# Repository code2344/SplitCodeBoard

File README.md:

# SplitCodeBoard

SplitCodeBoard is a split keyboard with a macropad designed for programming. I made this because I do not have any good keyboards at home, and the idea of a split keyboard appealed to me. 
SplitCodeBoard was made as part of Hack Club Stasis. "SplitCodeBoard.step" is the PCB STEP, the pcb with case is in 'SplitCodeBoard.step_STEP.zip'.
Here are some images: <br>
Macropad:<br>
<br>
Left keyboard half:<br>
<br>
Right keyboard half:<br>
<br>
Side schematic:<br>
<br>
Main and macropad schematic:<br>
<br>
PCB:<br>
<br>

## BOM
| Name | Purpose | Quantity | Total Cost (USD) | Link | Distributor |
|------|---------|----------|------------------|------|-------------|
| MCP23017-E/SO | GPIO expansion for the nRF52840 on the keyboard sides | 2 | 3.24 | [Link to listing](https://www.digikey.com/en/products/detail/microchip-technology/MCP23017-E-SO/894271) | Digikey |
| Seeed Xiao nRF52840 | Microcontrollers | 3 | 48.54 | [Link to listing](https://www.digikey.com.au/en/products/detail/seeed-technology-co-ltd/102010448/16652893?srsltid=AfmBOopCoDCC1iggG736AFU-o5CQ8K0FazSBUvREHLvtvnr260xrHbc02Ug) | Digikey |
| Kailh PG1350 Choc V1 70PCS Mechanical Keyboard Switch Kailh Low Profile Switches Chocolate Mechanical Keyboard Switch RGB SMD 5-Pin Kailh Switches | Switches for the keyboard | 1 | 49.98 | [Link to listing](https://snapklik.com/en-au/product/kailh-pg1350-choc-v1-70pcs-mechanical-keyboard-switch-kailh-low-profile-switches-chocolate-mechanical-keyboard-switch-rgb-smd-5-pin-kailh-switches-dark-blue-70pcs/0W3L4PV7UIYW5) | Snapklik |
| Kailh Choc Hotswap Sockets (Pack of 10) | Hotswap sockets for the keys | 7 | 24.5 | [Link to listing](https://keebd.com/products/kailh-choc-hotswap-sockets?variant=40393453338776&country=AU&currency=AUD) | KEEBD |
| PURFIELD 3.7V 501012 401010 401012 400909 Polymer Lithium Battery Suitable for I7 i8 i9 i10 Earphone Headset MP3 MP4 Toy GPS | Batteries for each half of the keyboard | 20 | 21.2 | [Link to listing](https://www.aliexpress.com/item/1005008747431465.html) | Aliexpress |
| 1N5819HW-7-F | Diodes for the key matrix | 70 | 17.15 | [Link to listing](https://www.digikey.com.au/en/products/detail/diodes-incorporated/1N5819HW-7-F/814970) | Digikey |

## Licensing

This repository uses split licensing by content type:

- Firmware and firmware configuration (for example, files under `zmk-config/`) are licensed under GNU Affero General Public License v3.0 only (`AGPL-3.0-only`).
- Hardware design files (for example, KiCad schematics/PCBs, footprints, and 3D mechanical files) are licensed under CERN Open Hardware Licence Version 2 - Strongly Reciprocal (`CERN-OHL-S-2.0`).

See the root `LICENSE` file for full licensing scope and notices.

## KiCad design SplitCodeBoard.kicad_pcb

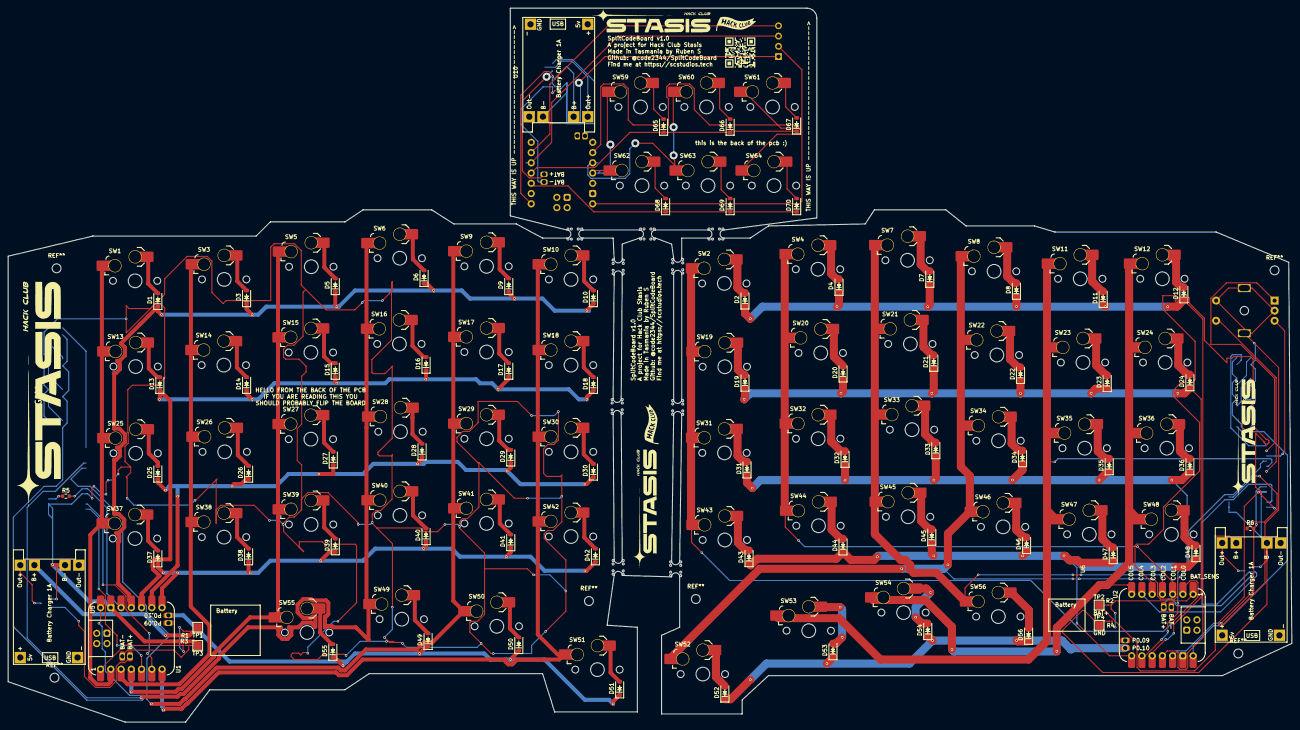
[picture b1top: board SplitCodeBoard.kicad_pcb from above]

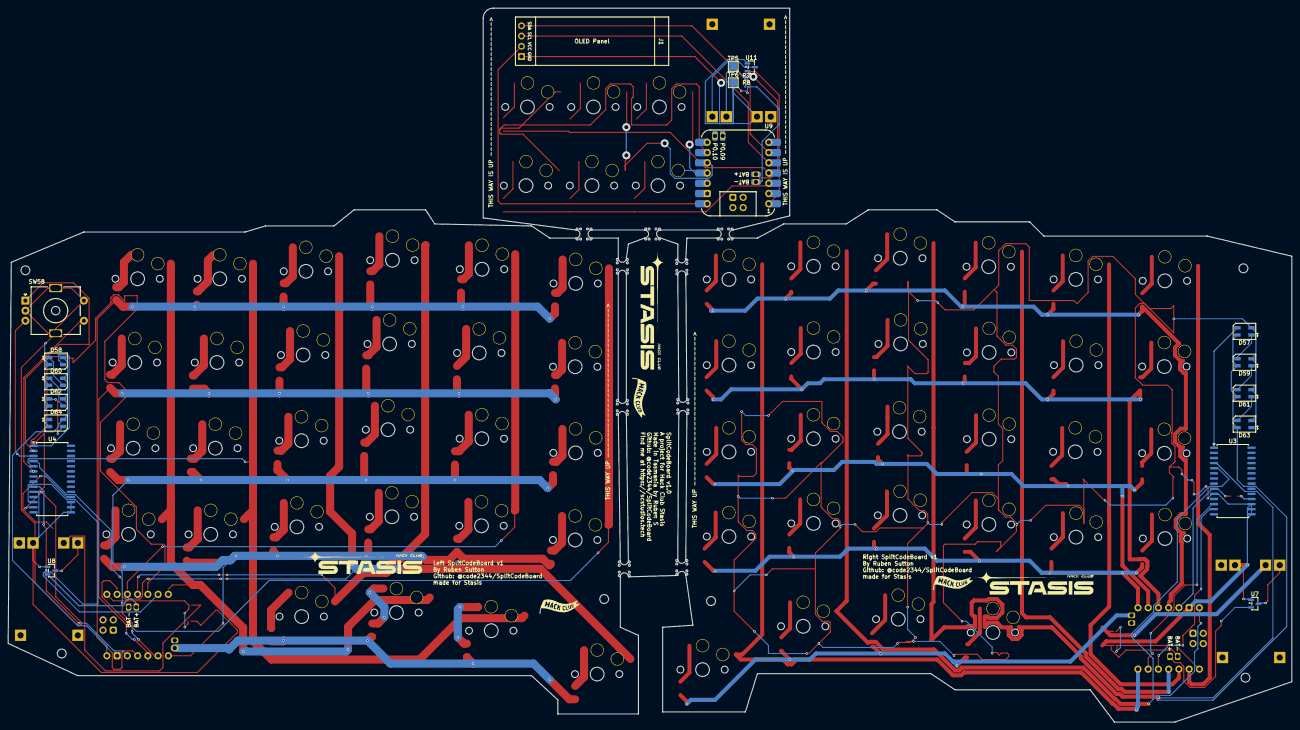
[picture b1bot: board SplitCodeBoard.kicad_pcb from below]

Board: 2 copper layers, 318.2 x 176.9 mm, 169 parts (20 on the bottom side), 124 nets.

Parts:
D1, D2, D3, D4, D5, D6, D7, D8, D9, D10, D11, D12, D13, D14, D15, D16, D17, D18, D19, D20, D21, D22, D23, D24, D25, D26, D27, D28, D29, D30, D31, D32, D33, D34, D35, D36, D37, D38, D39, D40, D41, D42, D43, D44, D45, D46, D47, D48, D49, D50, D51, D52, D53, D54, D55, D56, D65, D66, D67, D68, D69, D70: D; D_SOD-123
D57, D58, D59, D60, D61, D62, D63, D64: SK6812MINI; LED_SK6812MINI_PLCC4_3.5x3.5mm_P1.75mm
H1, H1#2, H1#3, H1#4, H1#5, H1#6, H1#7, H2, H3: MountingHole; MouseBite-Slot_2.0x2.0mm_inset_D0.5mm_P0.85mm_4h_Trace
J1: OLED; SSD1306-0.91-OLED-4pin-128x32
QR${REFERENCE}: https://scstudios.tech; httpsscstudios.tech
R1, R2, R3, R4, R7, R8: R; R_0201_0603Metric
R5, R6: 10k; R_0603_1608Metric
SW1, SW2, SW3, SW4, SW5, SW6, SW7, SW8, SW9, SW10, SW11, SW12, SW13, SW14, SW15, SW16, SW17, SW18, SW19, SW20, SW21, SW22, SW23, SW24, SW25, SW26, SW27, SW28, SW29, SW30, SW31, SW32, SW33, SW34, SW35, SW36, SW37, SW38, SW39, SW40, SW41, SW42, SW43, SW44, SW45, SW46, SW47, SW48, SW49, SW50, SW51, SW52, SW53, SW54, SW55, SW56, SW59, SW60, SW61, SW62, SW63, SW64: SW_Push; SW_choc_v1_HS_CPG135001S30_1u
SW58: RotaryEncoder_Switch_MP; RotaryEncoder_Alps_EC11E-Switch_Vertical_H20mm_MountingHoles
TP1, TP2, TP5: BAT; TestPoint_Pad_2.0x2.0mm
TP3, TP4, TP6: GND; TestPoint_Pad_2.0x2.0mm
U1, U2, U9: Seeeduino Xiao nRF52840; Xiao_nRF52840_ACH
U3, U4: MCP23017_SO; SOIC-28W_7.5x17.9mm_P1.27mm
U5, U6, U10: TP4056-18650
U7, U8, U11: MCP1700x-330xxTT; SOT-23

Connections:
+5V: D57.4 (VDD), D58.4 (VDD), D59.4 (VDD), D60.4 (VDD), D61.4 (VDD), D62.4 (VDD), D63.4 (VDD), D64.4 (VDD), J1.2, U1.8 (5V), U2.8 (5V), U9.8 (5V)
/3.3: U9.16 (BAT+), U11.2 (VO)
/BT_PIN: R7.2, R8.1, U9.1 (P0.02)
/COL1: SW59.1, SW62.1, U9.11 (P1.15)
/COL2: SW60.1, SW63.1, U9.12 (P1.14)
/COL3: SW61.1, SW64.1, U9.13 (P1.13)
/ROW1: D65.1 (K), D66.1 (K), D67.1 (K), U9.4 (P0.29)
/ROW2: D68.1 (K), D69.1 (K), D70.1 (K), U9.3 (P0.28)
/VBAT: R7.1, TP5.1, U10.5 (B+)
/left/3.3: U1.16 (BAT+), U7.2 (VO)
/left/BT_PIN: R1.2, R3.1, U1.1 (P0.02)
/left/COL0: SW1.1, SW13.1, SW25.1, SW37.1, U1.2 (P0.03)
/left/COL1: SW3.1, SW14.1, SW26.1, SW38.1, U1.3 (P0.28)
/left/COL2: SW5.1, SW15.1, SW27.1, SW39.1, SW55.1, U1.4 (P0.29)
/left/COL3: SW6.1, SW16.1, SW28.1, SW40.1, SW49.1, U3.4 (GPB3)
/left/COL4: SW9.1, SW17.1, SW29.1, SW41.1, SW50.1, U3.5 (GPB4)
/left/COL5: SW10.1, SW18.1, SW30.1, SW42.1, SW51.1, U1.7 (P1.11)
/left/ROW0: D1.1 (K), D3.1 (K), D5.1 (K), D6.1 (K), D9.1 (K), D10.1 (K), U1.11 (P1.15)
/left/ROW1: D13.1 (K), D14.1 (K), D15.1 (K), D16.1 (K), D17.1 (K), D18.1 (K), U1.12 (P1.14)
/left/ROW2: D25.1 (K), D26.1 (K), D27.1 (K), D28.1 (K), D29.1 (K), D30.1 (K), U1.13 (P1.13)
/left/ROW3: D37.1 (K), D38.1 (K), D39.1 (K), D40.1 (K), D41.1 (K), D42.1 (K), U1.14 (P1.12)
/left/ROW4: D49.1 (K), D50.1 (K), D51.1 (K), D55.1 (K), U1.18 (P0.10)
/left/VBAT: R1.1, TP1.1, U5.5 (B+)
/right/1A: SW58.A, U4.2 (GPB1)
/right/1B: SW58.B, U4.3 (GPB2)
/right/3.3: U2.16 (BAT+), U8.2 (VO)
/right/BT_PIN: R2.2, R4.1, U2.1 (P0.02)
/right/COL0: SW2.1, SW19.1, SW31.1, SW43.1, U2.2 (P0.03)
/right/COL1: SW4.1, SW20.1, SW32.1, SW44.1, U2.3 (P0.28)
/right/COL2: SW7.1, SW21.1, SW33.1, SW45.1, SW56.1, U2.4 (P0.29)
/right/COL3: SW8.1, SW22.1, SW34.1, SW46.1, SW52.1, U4.4 (GPB3)
/right/COL4: SW11.1, SW23.1, SW35.1, SW47.1, SW53.1, U4.5 (GPB4)
/right/COL5: SW12.1, SW24.1, SW36.1, SW48.1, SW54.1, U2.7 (P1.11)
/right/ROW0: D2.1 (K), D4.1 (K), D7.1 (K), D8.1 (K), D11.1 (K), D12.1 (K), U2.11 (P1.15)
/right/ROW1: D19.1 (K), D20.1 (K), D21.1 (K), D22.1 (K), D23.1 (K), D24.1 (K), U2.12 (P1.14)
/right/ROW2: D31.1 (K), D32.1 (K), D33.1 (K), D34.1 (K), D35.1 (K), D36.1 (K), U2.13 (P1.13)
/right/ROW3: D43.1 (K), D44.1 (K), D45.1 (K), D46.1 (K), D47.1 (K), D48.1 (K), U2.14 (P1.12)
/right/ROW4: D52.1 (K), D53.1 (K), D54.1 (K), D56.1 (K), U2.18 (P0.10)
/right/S1: SW58.S1, U4.6 (GPB5)
/right/VBAT: R2.1, TP2.1, U6.5 (B+)
GND: D57.2 (VSS), D58.2 (VSS), D59.2 (VSS), D60.2 (VSS), D61.2 (VSS), D62.2 (VSS), D63.2 (VSS), D64.2 (VSS), J1.1, R3.2, R4.2, R8.2, SW58.C, SW58.MP, SW58.S2, TP3.1, TP4.1, TP6.1, U1.9 (GND), U1.15 (BAT-), U2.9 (GND), U2.15 (BAT-), U3.10 (VSS), U3.15 (A0), U3.16 (A1), U3.17 (A2), U4.10 (VSS), U4.15 (A0), U4.16 (A1), U4.17 (A2), U5.6 (B-), U6.6 (B-), U7.1 (GND), U8.1 (GND), U9.15 (BAT-), U10.6 (B-), U11.1 (GND)
unnamed: D1.2 (A), SW1.2
unnamed: D2.2 (A), SW2.2
unnamed: D3.2 (A), SW3.2
unnamed: D4.2 (A), SW4.2
unnamed: D5.2 (A), SW5.2
unnamed: D6.2 (A), SW6.2
unnamed: D7.2 (A), SW7.2
unnamed: D8.2 (A), SW8.2
unnamed: D9.2 (A), SW9.2
unnamed: D10.2 (A), SW10.2
unnamed: D11.2 (A), SW11.2
unnamed: D12.2 (A), SW12.2
unnamed: D13.2 (A), SW13.2
unnamed: D14.2 (A), SW14.2
unnamed: D15.2 (A), SW15.2
unnamed: D16.2 (A), SW16.2
unnamed: D17.2 (A), SW17.2
unnamed: D18.2 (A), SW18.2
unnamed: D19.2 (A), SW19.2
unnamed: D20.2 (A), SW20.2
unnamed: D21.2 (A), SW21.2
unnamed: D22.2 (A), SW22.2
unnamed: D23.2 (A), SW23.2
unnamed: D24.2 (A), SW24.2
unnamed: D25.2 (A), SW25.2
unnamed: D26.2 (A), SW26.2
unnamed: D27.2 (A), SW27.2
unnamed: D28.2 (A), SW28.2
unnamed: D29.2 (A), SW29.2
unnamed: D30.2 (A), SW30.2
unnamed: D31.2 (A), SW31.2
unnamed: D32.2 (A), SW32.2
unnamed: D33.2 (A), SW33.2
unnamed: D34.2 (A), SW34.2
unnamed: D35.2 (A), SW35.2
unnamed: D36.2 (A), SW36.2
unnamed: D37.2 (A), SW37.2
unnamed: D38.2 (A), SW38.2
unnamed: D39.2 (A), SW39.2
unnamed: D40.2 (A), SW40.2
unnamed: D41.2 (A), SW41.2
unnamed: D42.2 (A), SW42.2
unnamed: D43.2 (A), SW43.2
unnamed: D44.2 (A), SW44.2
unnamed: D45.2 (A), SW45.2
unnamed: D46.2 (A), SW46.2
unnamed: D47.2 (A), SW47.2
unnamed: D48.2 (A), SW48.2
unnamed: D49.2 (A), SW49.2
unnamed: D50.2 (A), SW50.2
unnamed: D51.2 (A), SW51.2
unnamed: D52.2 (A), SW52.2
unnamed: D53.2 (A), SW53.2
unnamed: D54.2 (A), SW54.2
unnamed: D55.2 (A), SW55.2
unnamed: D56.2 (A), SW56.2
unnamed: D57.3 (DIN), U3.1 (GPB0)
unnamed: D57.1 (DOUT), D59.3 (DIN)
unnamed: D58.3 (DIN), U4.1 (GPB0)
unnamed: D58.1 (DOUT), D60.3 (DIN)
unnamed: D59.1 (DOUT), D61.3 (DIN)
unnamed: D60.1 (DOUT), D62.3 (DIN)
unnamed: D61.1 (DOUT), D63.3 (DIN)
unnamed: D62.1 (DOUT), D64.3 (DIN)
unnamed: D65.2 (A), SW59.2
unnamed: D66.2 (A), SW60.2
unnamed: D67.2 (A), SW61.2
unnamed: D68.2 (A), SW62.2
unnamed: D69.2 (A), SW63.2
unnamed: D70.2 (A), SW64.2
unnamed: J1.3, U9.5 (P0.04)
unnamed: J1.4, U9.6 (P0.05)
unnamed: R5.2, U1.10 (3V3), U3.9 (VDD)
unnamed: U1.5 (P0.04), U3.13 (SDA)
unnamed: U1.6 (P0.05), U3.12 (SCK)
unnamed: R6.2, U2.10 (3V3), U4.9 (VDD)
unnamed: U2.5 (P0.04), U4.13 (SDA)
unnamed: U2.6 (P0.05), U4.12 (SCK)
unnamed: R5.1, U3.18 (~RESET)
unnamed: R6.1, U4.18 (~RESET)
unnamed: U5.3 (Out+), U7.3 (VI)
unnamed: U6.3 (Out+), U8.3 (VI)
unnamed: U10.3 (Out+), U11.3 (VI)

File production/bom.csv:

Designator,Footprint,Quantity,Value,LCSC Part #
"D1, D10, D11, D12, D13, D14, D15, D16, D17, D18, D19, D2, D20, D21, D22, D23, D24, D25, D26, D27, D28, D29, D3, D30, D31, D32, D33, D34, D35, D36, D37, D38, D39, D4, D40, D41, D42, D43, D44, D45, D46, D47, D48, D49, D5, D50, D51, D52, D53, D54, D55, D56, D6, D65, D66, D67, D68, D69, D7, D70, D8, D9",D_SOD-123,62,D,
"D57, D58, D59, D60, D61, D62, D63, D64",LED_SK6812MINI_PLCC4_3.5x3.5mm_P1.75mm,8,SK6812MINI,
J1,SSD1306-0.91-OLED-4pin-128x32,1,OLED,
QR${REFERENCE},httpsscstudios.tech,1,https://scstudios.tech,
"R1, R2, R3, R4, R7, R8",0201,6,R,
"R5, R6",0603,2,10k,
"SW1, SW10, SW11, SW12, SW13, SW14, SW15, SW16, SW17, SW18, SW19, SW2, SW20, SW21, SW22, SW23, SW24, SW25, SW26, SW27, SW28, SW29, SW3, SW30, SW31, SW32, SW33, SW34, SW35, SW36, SW37, SW38, SW39, SW4, SW40, SW41, SW42, SW43, SW44, SW45, SW46, SW47, SW48, SW49, SW5, SW50, SW51, SW52, SW53, SW54, SW55, SW56, SW59, SW6, SW60, SW61, SW62, SW63, SW64, SW7, SW8, SW9",SW_choc_v1_HS_CPG135001S30_1u,62,SW_Push,
SW58,RotaryEncoder_Alps_EC11E-Switch_Vertical_H20mm_MountingHoles,1,RotaryEncoder_Switch_MP,
"TP1, TP2, TP5",TestPoint_Pad_2.0x2.0mm,3,BAT,
"TP3, TP4, TP6",TestPoint_Pad_2.0x2.0mm,3,GND,
"U10, U5, U6",TP4056-18650,3,~,
"U11, U7, U8",SOT-23,3,MCP1700x-330xxTT,
"U3, U4",SOIC-28W_7.5x17.9mm_P1.27mm,2,MCP23017_SO,

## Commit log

2026-03-12 more stuff
2026-03-15 Create LICENSE
2026-03-15 Flatten zmk-config into main repository
2026-03-15 Clean source control artifacts after repo flatten
2026-03-15 Add SplitCodeBoard macropad support and configuration files
    - Created package.json to include dependency on xpm.
    - Added Kconfig for SplitCodeBoard macropad to define board configuration.
    - Documented layout and wiring notes for the SplitCodeBoard in layouts file.
    - Created device tree overlay for SplitCodeBoard macropad with GPIO configurations.
    - Added default configuration file for SplitCodeBoard macropad enabling GPIO and BLE support.
    - Added a lock file for the SplitCodeBoard schematic.
2026-03-15 Add licensing information and copyright headers to project files
2026-03-31 Uploading BOM
2026-03-31 Update journal entry generation note
2026-03-31 Added Case
2026-03-31 renamed folder
2026-03-31 added fake firmware
2026-03-31 Rename Split CodeBoard-bom.csv to BOM.csv
2026-03-31 moved pcb stuff to a folder
